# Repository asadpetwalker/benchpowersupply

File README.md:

# benchpowersupply

# What it is

A 500W Variable PSU with real time CC/CV error correction, current clamping, a 16 bit DAC for millivolt and milliamp precision. 

# Why I Made This
Precision power supplies are really cool, and high power power supplies are also really cool, some precision PSUs having milliamp/millivolt precision, and some high power PSUs going upto 2kW, but I couldn't find a single power supply with more than 300W with sub volt precision for under a lot of money, and I've always wanted to design one since they're really impressive, so I did. 

# Pictures

# BOM

| Item | Purpose | Qty | Cost | Link |
| :--- | :--- | :---: | :---: | :--- |
| **FC4L90R002FER** | CURRENT SENSE CHIP 1% 0.002 OHM | 5 | $13.75 | - |
| **8174** | TERM SCREW 10-32 4 PIN PCB | 4 | $5.56 | - |
| **FCR7350Y** | 4MM PANEL SKT S16N-PC YELLOW | 2 | $15.74 | - |
| **FCR7350B** | 4MM PANEL SKT S16N-PC BLACK | 2 | $15.32 | - |
| **INA238AQDGSRQ1** | IC PWR MONITOR 10VSSOP | 2 | $9.00 | - |
| **411019-01** | CORD 14AWG NEMA 5-15P TO CBL 10' | 2 | $35.12 | - |
| **0190700090** | CONN RING CIRC 14-16AWG #10 | 6 | $1.32 | - |
| **LM5149RGYR** | 800mV~55V Adjustable Step-down DC DC Controller | 2 | $7.96 | [LCSC](https://www.lcsc.com/product-detail/C7528454.html) |
| **LM5164DDAR** | 1MHz Step-down Adjustable 1A Voltage Regulator | 2 | $0.00 | [LCSC](https://www.lcsc.com/product-detail/C477928.html) |
| **ESP32-S3-WROOM-1-N4** | 2.4GHz ESP32-S3 On-board PCB Antenna Module | 2 | $8.30 | [LCSC](https://www.lcsc.com/product-detail/C2913197.html) |
| **ADS8681IRUMR** | SPI 4.75V~5.25V WQFN-16 Analog to Digital Converter | 2 | $19.80 | [LCSC](https://www.lcsc.com/product-detail/C2670107.html) |
| **REF6025IDGKR** | Series Voltage Reference IC Fixed 2.5V ±0.05% | 2 | $11.72 | [LCSC](https://www.lcsc.com/product-detail/C2157015.html) |
| **DAC8562SDGSR** | 10us 2.7V~5.5V Digital to Analog Converter | 2 | $21.98 | [LCSC](https://www.lcsc.com/product-detail/C127965.html) |
| **INA241A4IDR** | -5V~110V 100V/V Instrumentation / Current Sense Amp | 2 | $7.11 | [LCSC](https://www.lcsc.com/product-detail/C22427873.html) |
| **TLV3501AIDR** | Rail-to-Rail Input/Output SOP-8 Comparator | 2 | $7.00 | [LCSC](https://www.lcsc.com/product-detail/C43484.html) |
| **SER2915H-223KL** | 30A 22uH ±10% Shielded Inductor SMD | 2 | $17.71 | [LCSC](https://www.lcsc.com/product-detail/C19276066.html) |
| **BSC027N10NS5** | N-Channel 100V 3W Surface Mount MOSFET | 2 | $9.80 | [LCSC](https://www.lcsc.com/product-detail/C534315.html) |
| **BSC040N10NS5** | 100V 86A 139W Surface Mount MOSFET | 2 | $1.96 | [LCSC](https://www.lcsc.com/product-detail/C534334.html) |
| **AP2112K-3.3TRG1** | 3.3V Positive Fixed LDO Regulator (TECH PUBLIC) | 5 | $0.00 | [LCSC](https://www.lcsc.com/product-detail/C23380830.html) |
| **AP2112K-3.3TRG1** | 3.3V Positive Fixed LDO Regulator (DIODES) | 5 | $0.00 | [LCSC](https://www.lcsc.com/product-detail/C51118.html) |
| **CC0805KRX7R9BB104** | 100nF ±10% 50V Ceramic Capacitor X7R 0805 | 20 | $0.39 | [LCSC](https://www.lcsc.com/product-detail/C49678.html) |
| **CL21B104KBCNNNC** | 100nF ±10% 50V Ceramic Capacitor X7R 0805 | 20 | $0.30 | [LCSC](https://www.lcsc.com/product-detail/C1711.html) |
| **CL21B105KBFNNNE** | 1uF ±10% 50V Ceramic Capacitor X7R 0805 | 20 | $0.81 | [LCSC](https://www.lcsc.com/product-detail/C28323.html) |
| **0805B222K500NT** | 2.2nF ±10% 50V Ceramic Capacitor X7R 0805 | 20 | $0.12 | [LCSC](https://www.lcsc.com/product-detail/C36576.html) |
| **CC0805JRNPO9BN560** | 56pF ±5% 50V Ceramic Capacitor NP0 0805 | 50 | $0.66 | [LCSC](https://www.lcsc.com/product-detail/C113831.html) |
| **HGC0805R5475K500NSLJ** | 4.7uF ±10% 50V Ceramic Capacitor X5R 0805 | 10 | $0.49 | [LCSC](https://www.lcsc.com/product-detail/C7472969.html) |
| **CL21A106KAYNNNE** | 10uF ±10% 25V Ceramic Capacitor X5R 0805 | 20 | $1.60 | [LCSC](https://www.lcsc.com/product-detail/C15850.html) |
| **0805CG101J500NT** | 100pF ±5% 50V Ceramic Capacitor C0G 0805 | 50 | $0.48 | [LCSC](https://www.lcsc.com/product-detail/C82028.html) |
| **HGC0805R5476M100NSLJ** | 47uF ±20% 10V Ceramic Capacitor X5R 0805 | 5 | $0.81 | [LCSC](https://www.lcsc.com/product-detail/C19103846.html) |
| **1210B104K251CT** | 100nF ±10% 250V Ceramic Capacitor X7R 1210 | 10 | $0.59 | [LCSC](https://www.lcsc.com/product-detail/C304007.html) |
| **EFVH100ADA101M10C0** | 100uF ±20% 100V Aluminum Electrolytic Capacitor | 5 | $1.15 | [LCSC](https://www.lcsc.com/product-detail/C22387799.html) |
| **CL21B102KBCNNNC** | 1nF ±10% 50V Ceramic Capacitor X7R 0805 | 20 | $0.30 | [LCSC](https://www.lcsc.com/product-detail/C46653.html) |
| **2N7002** | N-Channel 60V 115mA 200mW MOSFET SOT-23 | 50 | $0.56 | [LCSC](https://www.lcsc.com/product-detail/C916396.html) |
| **FRC0603F8872TS** | 88.7kΩ ±1% 100mW 0603 Thick Film Resistor | 100 | $0.27 | [LCSC](https://www.lcsc.com/product-detail/C2999456.html) |
| **FRC0603F1072TS** | 10.7kΩ ±1% 100mW 0603 Thick Film Resistor | 100 | $0.23 | [LCSC](https://www.lcsc.com/product-detail/C5153968.html) |
| **RC0603FR-07100KL** | 100kΩ ±1% 100mW 0603 Thick Film Resistor | 100 | $0.23 | [LCSC](https://www.lcsc.com/product-detail/C14675.html) |
| **FRC0603F3163TS** | 316kΩ ±1% 100mW 0603 Thick Film Resistor | 100 | $0.23 | [LCSC](https://www.lcsc.com/product-detail/C2998125.html) |
| **FRC0603F4703TS** | 470kΩ ±1% 100mW 0603 Thick Film Resistor | 100 | $0.21 | [LCSC](https://www.lcsc.com/product-detail/C2907040.html) |
| **HoJLR2512-3W-5mR-1%** | 5mΩ 3W Current Sense Resistor ±1% 2512 | 5 | $0.45 | [LCSC](https://www.lcsc.com/product-detail/C2903482.html) |
| **FRC0603F6193TS** | 619kΩ ±1% 100mW 0603 Thick Film Resistor | 100 | $0.13 | [LCSC](https://www.lcsc.com/product-detail/C5713292.html) |
| **RC0603FR-0710KL** | 10kΩ ±1% 100mW 0603 Thick Film Resistor | 100 | $0.35 | [LCSC](https://www.lcsc.com/product-detail/C98220.html) |
| **FRC0603F1502TS** | 15kΩ ±1% 100mW 0603 Thick Film Resistor | 100 | $0.22 | [LCSC](https://www.lcsc.com/product-detail/C2906995.html) |
| **AR05BTCW4003** | 400kΩ ±0.1% 125mW 0805 Thin Film Resistor | 20 | $0.94 | [LCSC](https://www.lcsc.com/product-detail/C3013969.html) |
| **FRC0603J102 TS** | 1kΩ ±5% 100mW 0603 Thick Film Resistor | 100 | $0.24 | [LCSC](https://www.lcsc.com/product-detail/C2907113.html) |
| **FRC0603J472 TS** | 4.7kΩ ±5% 100mW 0603 Thick Film Resistor | 100 | $0.21 | [LCSC](https://www.lcsc.com/product-detail/C2907166.html) |
| **RS-03K2701FT** | 2.7kΩ ±1% 100mW 0603 Thick Film Resistor | 100 | $0.20 | [LCSC](https://www.lcsc.com/product-detail/C118394.html) |
| **HRC0603F5101ENTN** | 5.1kΩ ±1% 100mW 0603 Thick Film Resistor | 100 | $0.12 | [LCSC](https://www.lcsc.com/product-detail/C54920932.html) |
| **1RC0603J0101** | 100Ω ±5% 100mW 0603 Thick Film Resistor | 100 | $0.17 | [LCSC](https://www.lcsc.com/product-detail/C54531636.html) |
| **EC11E15244B2** | Through Hole Encoder | 4 | $9.59 | [LCSC](https://www.lcsc.com/product-detail/C470754.html) |
| **SMMS0650-680M** | 1.5A 68uH ±20% Molded Inductor SMD | 5 | $0.89 | [LCSC](https://www.lcsc.com/product-detail/C2894721.html) |
| **SMPS** | 600W 60V SMPS PSU | 1 | 31.99 | [Amazon](https://www.amazon.com/NUOWEIDE-Converter-Transformer-Controller-Electric/dp/B0FTYPPZPR/ref=sr_1_5?sr=8-5)

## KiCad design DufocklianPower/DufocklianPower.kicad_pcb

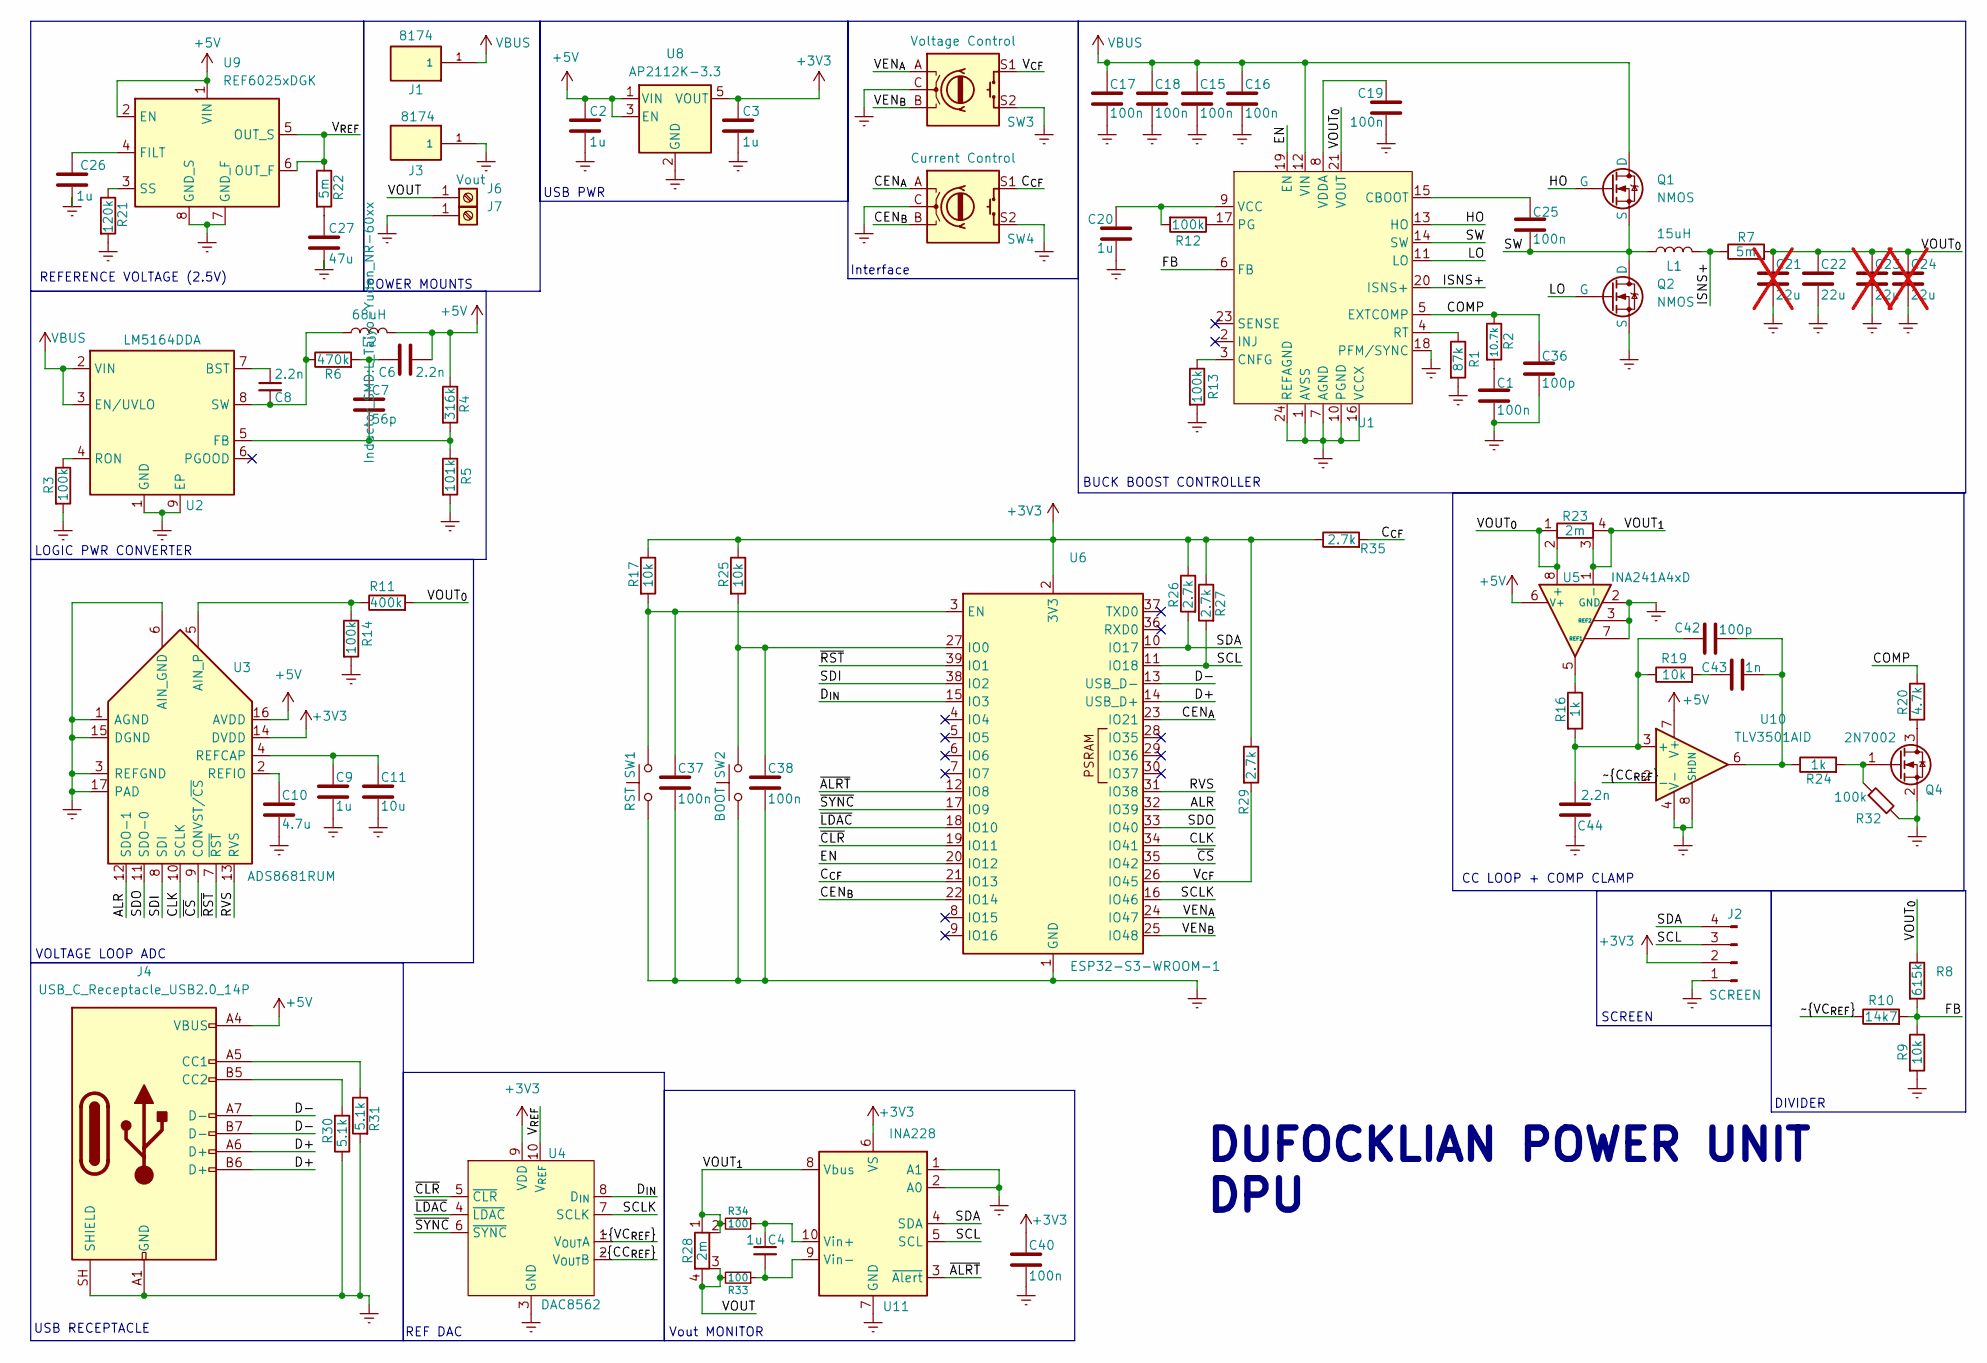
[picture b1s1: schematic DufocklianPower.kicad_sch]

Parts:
C1, C19, C25, C37, C38, C40: 100n; C_0805_2012Metric
C2, C3, C4, C9, C20, C26: 1u; C_0805_2012Metric
C6, C8, C44: 2.2n; C_0805_2012Metric
C7: 56p; C_0805_2012Metric
C10: 4.7u; C_0805_2012Metric
C11: 10u; C_0805_2012Metric
C15, C16, C17, C18: 100n; C_1210_3225Metric
C21: 22u; C_Elec_10x10.2; not fitted
C22: 22u; C_Elec_10x10.2
C23, C24: 22u; C_2220_5750Metric; not fitted
C27: 47u; C_0805_2012Metric
C36, C42: 100p; C_0805_2012Metric
C43: 1n; C_0805_2012Metric
J1, J3: 8174; KEYSTONE_8174; PARTREV B
J2: SCREEN; PinHeader_1x04_P2.54mm_Vertical
J4: USB_C_Receptacle_USB2.0_14P; USB_C_Receptacle_GCT_USB4105-xx-A_16P_TopMnt_Horizontal
J6: Vout; Banana_Cliff_FCR7350Y_S16N-PC_Horizontal
J7: Screw_Terminal_01x01; Banana_Cliff_FCR7350Y_S16N-PC_Horizontal
L1: 15uH; IND_SER2915H-223KL
L2: 68uH; L_Taiyo-Yuden_NR-60xx
Q1, Q2: NMOS; TRANS_BSC027N10NS5ATMA1
Q4: 2N7002; SOT-23
R1: 87k; R_0603_1608Metric
R2: 10.7k; R_0603_1608Metric
R3, R12, R13, R14, R32: 100k; R_0603_1608Metric
R4: 316k; R_0603_1608Metric
R5: 101k; R_0603_1608Metric
R6: 470k; R_0603_1608Metric
R7: 5m; R_2512_6332Metric
R8: 615k; R_0603_1608Metric
R9, R17, R19, R25: 10k; R_0603_1608Metric
R10: 14k7; R_0603_1608Metric
R11: 400k; R_0805_2012Metric
R16, R24: 1k; R_0603_1608Metric
R20: 4.7k; R_0603_1608Metric
R21: 120k; R_0603_1608Metric
R22: 5m; R_0603_1608Metric
R23, R28: 2m; FC4L90_OHM
R26, R27, R29, R35: 2.7k; R_0603_1608Metric
R30, R31: 5.1k; R_0603_1608Metric
R33, R34: 100; R_0603_1608Metric
SW1: RST; SW_Push_1P1T-SH_NO_CK_KMR2xxG
SW2: BOOT; SW_Push_1P1T-SH_NO_CK_KMR2xxG
SW3: Voltage Control; RotaryEncoder_Alps_EC11E-Switch_Vertical_H20mm
SW4: Current Control; RotaryEncoder_Alps_EC11E-Switch_Vertical_H20mm
U1: VQFN24_RGY_TEX
U2: LM5164DDA; HSOP-8-1EP_3.9x4.9mm_P1.27mm_EP2.41x3.1mm_ThermalVias
U3: ADS8681RUM; QFN-16-1EP_4x4mm_P0.65mm_EP2.7x2.7mm
U4: DAC8562; TSSOP-10_3x3mm_P0.5mm
U5: INA241A4xD; SOIC-8_3.9x4.9mm_P1.27mm
U6: ESP32-S3-WROOM-1
U8: AP2112K-3.3; SOT-23-5
U9: REF6025xDGK; VSSOP-8_3x3mm_P0.65mm
U10: TLV3501AID; SOIC-8_3.9x4.9mm_P1.27mm
U11: INA228; TSSOP-10_3x3mm_P0.5mm

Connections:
+5V: C2.1, C6.2, J4.A4 (VBUS), J4.A9 (VBUS), J4.B4 (VBUS), J4.B9 (VBUS), L2.2, R4.1, U3.16 (AVDD), U5.6 (V+), U8.1 (VIN), U8.3 (EN), U9.1 (VIN), U9.2 (EN), U10.7 (V+)
/ALR: U3.12 (SDO-1), U6.32 (IO39)
/CEN_{A}: SW4.A, U6.23 (IO21)
/CEN_{B}: SW4.B, U6.22 (IO14)
/CLK: U3.10 (SCLK), U6.34 (IO41)
/COMP: C36.1, R2.1, R20.1, U1.5 (EXTCOMP)
/C_{CF}: R35.2, SW4.S1, U6.21 (IO13)
/D+: J4.A6 (D+), J4.B6 (D+), U6.14 (USB_D+)
/D-: J4.A7 (D-), J4.B7 (D-), U6.13 (USB_D-)
/D_{IN}: U4.8 (D_{IN}), U6.15 (IO3)
/EN: U1.19 (EN), U6.20 (IO12)
/FB: R8.2, R9.1, R10.2, U1.6 (FB)
/HO: Q1.2 (G), U1.13 (HO)
/ISNS+: L1.2, R7.1, U1.20 (ISNS+)
/LO: Q2.2 (G), U1.11 (LO)
/RVS: U3.13 (RVS), U6.31 (IO38)
/SCL: J2.3, R27.2, U6.11 (IO18), U11.5 (SCL)
/SCLK: U4.7 (SCLK), U6.16 (IO46)
/SDI: U3.8 (SDI), U6.38 (IO2)
/SDO: U3.11 (SDO-0), U6.33 (IO40)
/SW: C25.2, L1.1, Q1.3 (S), Q2.1 (D), U1.14 (SW)
/VEN_{A}: SW3.A, U6.24 (IO47)
/VEN_{B}: SW3.B, U6.25 (IO48)
/VOUT: J6.1 (Pin_1_1), R28.3, R28.4, R33.2
/VOUT_{0}: C21.1, C22.1, C23.1, C24.1, R7.2, R8.1, R11.2, R23.1, R23.2, U1.21 (VOUT), U5.8 (+)
/VOUT_{1}: R23.3, R23.4, R28.1, R28.2, R34.2, U5.1 (-), U11.8 (Vbus)
/V_{CF}: R29.2, SW3.S1, U6.26 (IO45)
/V_{REF}: R22.1, U4.10 (V_{REF}), U9.5 (OUT_S), U9.6 (OUT_F)
/~ALRT: U6.12 (IO8), U11.3 (~Alert)
/~CC_{REF}: U4.2 (V_{OUT}B), U10.2 (-)
/~CLR: U4.5 (~CLR), U6.19 (IO11)
/~CS: U3.9 (CONVST/~CS), U6.35 (IO42)
/~LDAC: U4.4 (~LDAC), U6.18 (IO10)
/~RST: U3.7 (~RST), U6.39 (IO1)
/~SYNC: U4.6 (~SYNC), U6.17 (IO9)
/~VC_{REF}: R10.1, U4.1 (V_{OUT}A)
GNDREF: C1.2, C2.2, C3.2, C9.1, C10.1, C11.1, C15.2, C16.2, C17.2, C18.2, C19.2, C20.2, C21.2, C22.2, C23.2, C24.2, C26.2, C27.2, C36.2, C37.2, C38.2, C40.2, C44.1, J2.1, J3.1, J3.2 (1__1), J3.3 (1__2), J3.4 (1__3), J4.A1 (GND), J4.A12 (GND), J4.B1 (GND), J4.B12 (GND), J4.SH (SHIELD), J7.1 (Pin_1_1), Q2.3 (S), Q4.2 (S), R1.2, R3.2, R5.2, R9.2, R13.2, R14.2, R21.2, R30.1, R31.2, R32.2, SW1.1, SW2.1, SW3.C, SW3.S2, SW4.C, SW4.S2, U1.1 (AVSS), U1.7 (AGND), U1.10 (PGND), U1.16 (VCCX), U1.18 (PFM/SYNC), U1.24 (REFAGND), U1.25 (GND), U2.1 (GND), U2.9 (EP), U3.1 (AGND), U3.3 (REFGND), U3.6 (AIN_GND), U3.15 (DGND), U3.17 (PAD), U4.3 (GND), U5.2 (GND), U5.3 (REF2), U5.4 (GND), U5.7 (REF1), U6.1 (GND), U6.40 (GND), U6.41 (GND), U8.2 (GND), U9.7 (GND_F), U9.8 (GND_S), U10.4 (V-), U10.8 (SHDN), U11.1 (A1), U11.2 (A0), U11.7 (GND)
unnamed: C1.1, R2.2
unnamed: C6.1, C7.2, R6.2
unnamed: C27.1, R22.2
unnamed: C42.2, C43.2, R24.1, U10.6
unnamed: C43.1, R19.2
unnamed: J4.A5 (CC1), R31.1
unnamed: J4.B5 (CC2), R30.2
unnamed: Q4.3 (D), R20.2
unnamed: Q4.1 (G), R24.2, R32.1
unnamed: R16.1, U5.5
unnamed: C25.1, U1.15 (CBOOT)
unnamed: R13.1, U1.3 (CNFG)
unnamed: R12.1, U1.17 (PG)
unnamed: R1.1, U1.4 (RT)
unnamed: C20.1, R12.2, U1.9 (VCC)
unnamed: C19.1, U1.8 (VDDA)
unnamed: C8.1, U2.7 (BST)
unnamed: C7.1, R4.2, R5.1, U2.5 (FB)
unnamed: R3.1, U2.4 (RON)
unnamed: C8.2, L2.1, R6.1, U2.8 (SW)
unnamed: R11.1, R14.1, U3.5 (AIN_P)
unnamed: C9.2, C11.2, U3.4 (REFCAP)
unnamed: C10.2, U3.2 (REFIO)
unnamed: C37.1, R17.2, SW1.2, U6.3 (EN)
unnamed: C38.1, R25.2, SW2.2, U6.27 (IO0)
unnamed: C26.1, U9.4 (FILT)
unnamed: R21.1, U9.3 (SS)
unnamed: C42.1, C44.2, R16.2, R19.1, U10.3 (+)
unnamed: C4.1, R34.1, U11.10 (Vin+)
unnamed: C4.2, R33.1, U11.9 (Vin-)
VBUS: C15.1, C16.1, C17.1, C18.1, J1.1, J1.2 (1__1), J1.3 (1__2), J1.4 (1__3), Q1.1 (D), U1.12 (VIN), U2.2 (VIN), U2.3 (EN/UVLO)

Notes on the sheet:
CC LOOP + COMP CLAMP
POWER MOUNTS
VOLTAGE LOOP ADC
Vout MONITOR
REFERENCE VOLTAGE (2.5V)
LOGIC PWR CONVERTER
SCREEN
DUFOCKLIAN POWER UNIT DPU
Interface
REF DAC
USB PWR
BUCK BOOST CONTROLLER
USB RECEPTACLE
DIVIDER

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
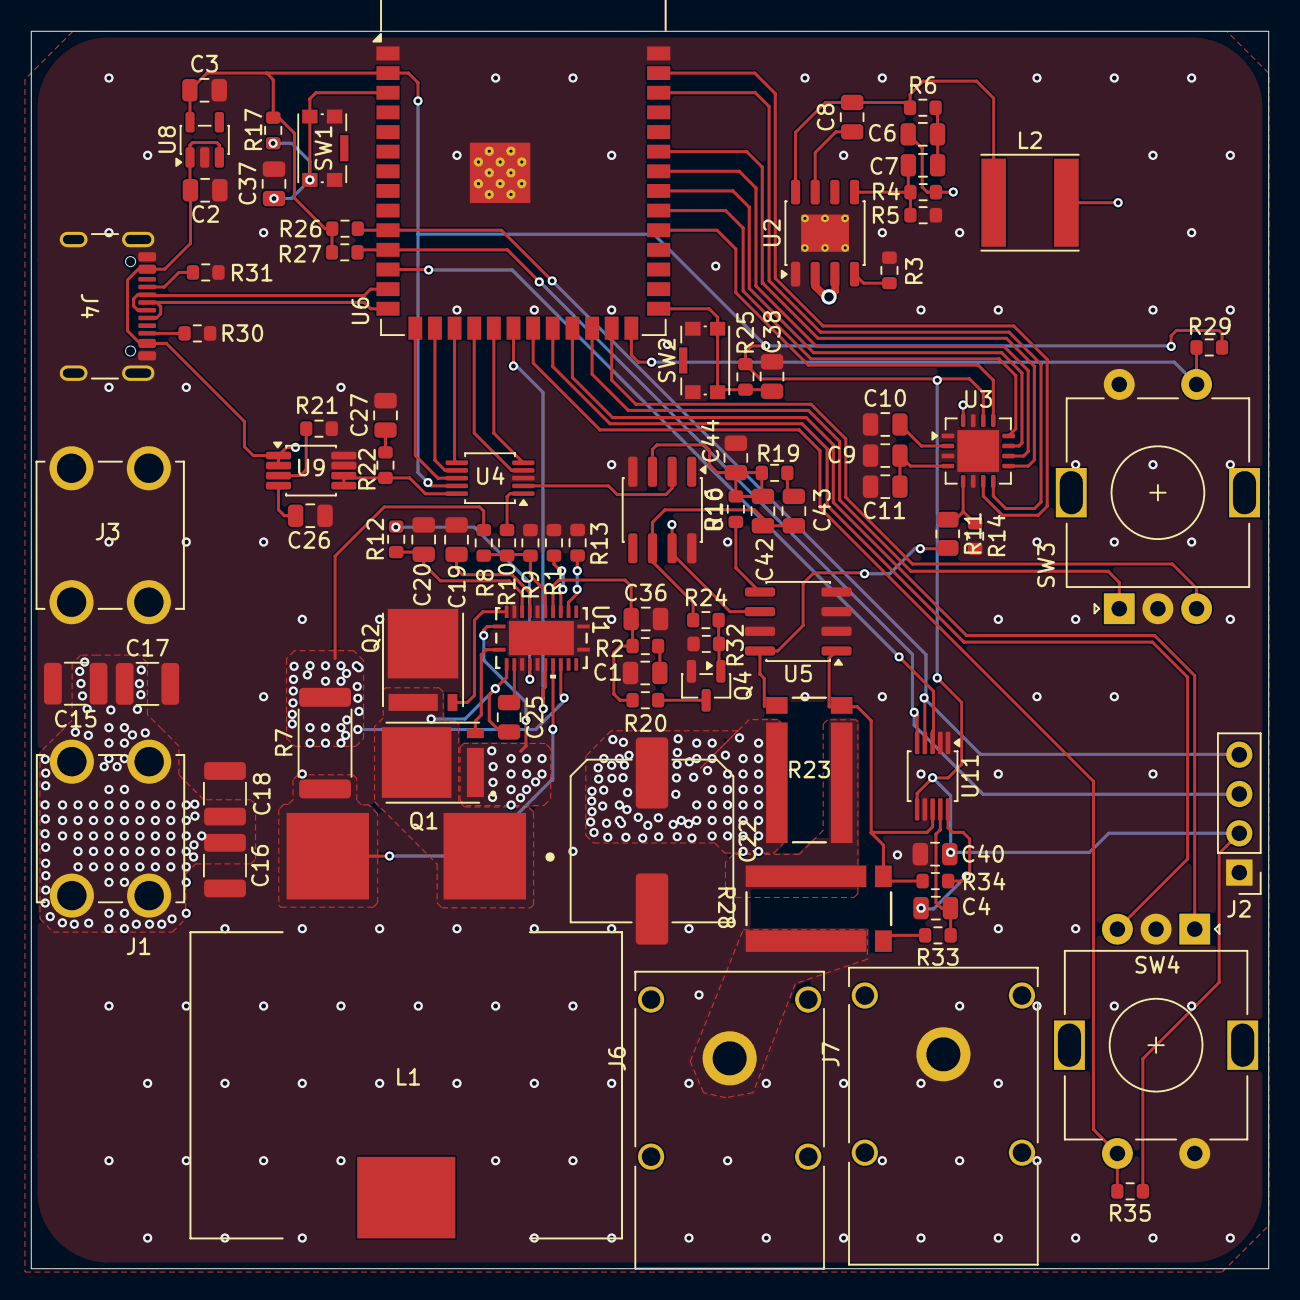
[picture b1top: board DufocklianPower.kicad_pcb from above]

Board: 4 copper layers, 80.0 x 80.0 mm, 85 parts (0 on the bottom side), 70 nets.
